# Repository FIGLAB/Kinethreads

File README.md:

# Kinethreads: Soft Full-Body Haptic Exosuit using Low-Cost Motor-Pulley Mechanisms
This is the repository for Kinethreads, presented at UIST 2025. Check out the [full paper here](https://drive.google.com/file/d/1RWJZLoprh9HyUMLJXVf4V8MswR2cnfrb/view?usp=sharing), as well as our [video](https://www.youtube.com/watch?v=4ev0w_tbuw8)!

Codebase will be updated soon!

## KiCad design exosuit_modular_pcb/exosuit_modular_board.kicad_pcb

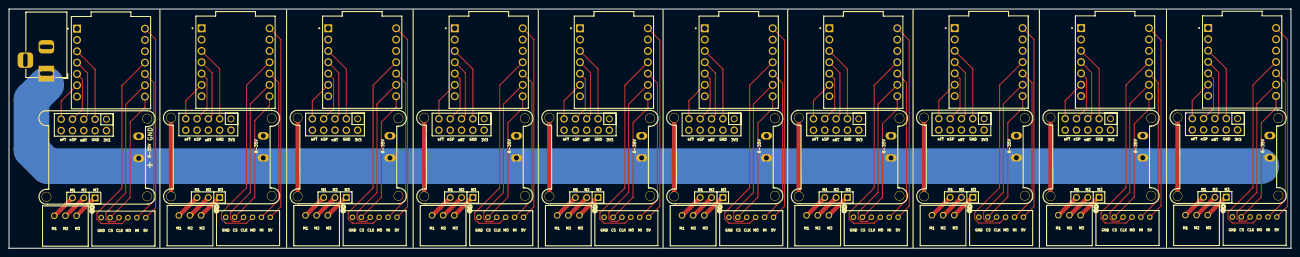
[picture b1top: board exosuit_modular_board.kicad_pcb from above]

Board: 2 copper layers, 287.6 x 53.7 mm, 56 parts (0 on the bottom side), 122 nets.

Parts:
BJ1: Barrel_Jack_Switch_Pin3Ring; BarrelJack_Horizontal
H1, H2, H3, H4, H5, H6, H7, H8, H9, H10: Female header2.54mm2*5p Straight; HDR-TH_10P-P2.54-V-F-R2-C5-S2.54
J1m1, J2m1, J3m1, J4m1, J5m1, J6m1, J7m1, J8m1, J9m1, J10m1: S3B-EH; CONN_S3B-EH_JST
J1s1, J2s1, J3s1, J4s1, J5s1, J6s1, J7s1, J8s1, J9s1, J10s1: S6B-PH-K-S; CONN_S6B-PH-K-S_JST
P1, P2, P3, P4, P5, P6, P7, P8, P9, P10: Header-Female-2.54_1x3; HDR-TH_3P-P2.54-V-F
Pad_gge5124: Pad_gge5124
Pad_gge5154: Pad_gge5154
Pad_gge5250: Pad_gge5250
Pad_gge5349: Pad_gge5349
Pad_gge7437: Pad_gge7437
U1, U2, U3, U4, U5, U6, U7, U8, U9, U10: ADAFRUIT_QT_PY; MODULE_ADAFRUIT_QT_PY

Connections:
GND: BJ1.2, BJ1.3, H1.1, H2.1, H3.1, H4.1, H5.1, H6.1, H7.1, H8.1, H9.1, H10.1, J1s1.1, J2s1.1, J3s1.1, J4s1.1, J5s1.1, J6s1.1, J7s1.1, J8s1.1, J9s1.1, J10s1.1, Pad_gge5124.2, Pad_gge5250.5, Pad_gge5349.5, Pad_gge7437.5, U1.13 (GND), U2.13 (GND), U3.13 (GND), U4.13 (GND), U5.13 (GND), U6.13 (GND), U7.13 (GND), U8.13 (GND), U9.13 (GND), U10.13 (GND)
unnamed: J1m1.1, P1.1
unnamed: J1m1.2, P1.2
unnamed: J1m1.3, P1.3
unnamed: J2m1.1, P2.1
unnamed: J2m1.2, P2.2
unnamed: J2m1.3, P2.3
unnamed: J3m1.1, P3.1
unnamed: J3m1.2, P3.2
unnamed: J3m1.3, P3.3
unnamed: J4m1.1, P4.1
unnamed: J4m1.2, P4.2
unnamed: J4m1.3, P4.3
unnamed: J5m1.1, P5.1
unnamed: J5m1.2, P5.2
unnamed: J5m1.3, P5.3
unnamed: J6m1.1, P6.1
unnamed: J6m1.2, P6.2
unnamed: J6m1.3, P6.3
unnamed: J7m1.1, P7.1
unnamed: J7m1.2, P7.2
unnamed: J7m1.3, P7.3
unnamed: J8m1.1, P8.1
unnamed: J8m1.2, P8.2
unnamed: J8m1.3, P8.3
unnamed: J9m1.1, P9.1
unnamed: J9m1.2, P9.2
unnamed: J9m1.3, P9.3
unnamed: J10m1.1, P10.1
unnamed: J10m1.2, P10.2
unnamed: J10m1.3, P10.3
unnamed: J1s1.6, U1.14 (5V)
unnamed: H1.3, U1.3 (A2/D2)
unnamed: H1.5, U1.4 (A3/D3)
unnamed: J1s1.2, U1.8 (A7/D7/RX)
unnamed: J1s1.3, U1.9 (A8/D8/SCK)
unnamed: J1s1.5, U1.10 (A9/D9/MISO)
unnamed: J1s1.4, U1.11 (A10/D10/MOSI)
unnamed: H1.7, U1.5 (D4/SDA)
unnamed: H1.9, U1.6 (D5/SCL)
unnamed: J2s1.6, U2.14 (5V)
unnamed: H2.3, U2.3 (A2/D2)
unnamed: H2.5, U2.4 (A3/D3)
unnamed: J2s1.2, U2.8 (A7/D7/RX)
unnamed: J2s1.3, U2.9 (A8/D8/SCK)
unnamed: J2s1.5, U2.10 (A9/D9/MISO)
unnamed: J2s1.4, U2.11 (A10/D10/MOSI)
unnamed: H2.7, U2.5 (D4/SDA)
unnamed: H2.9, U2.6 (D5/SCL)
unnamed: J3s1.6, U3.14 (5V)
unnamed: H3.3, U3.3 (A2/D2)
unnamed: H3.5, U3.4 (A3/D3)
unnamed: J3s1.2, U3.8 (A7/D7/RX)
unnamed: J3s1.3, U3.9 (A8/D8/SCK)
unnamed: J3s1.5, U3.10 (A9/D9/MISO)
unnamed: J3s1.4, U3.11 (A10/D10/MOSI)
unnamed: H3.7, U3.5 (D4/SDA)
unnamed: H3.9, U3.6 (D5/SCL)
unnamed: J4s1.6, U4.14 (5V)
unnamed: H4.3, U4.3 (A2/D2)
unnamed: H4.5, U4.4 (A3/D3)
unnamed: J4s1.2, U4.8 (A7/D7/RX)
unnamed: J4s1.3, U4.9 (A8/D8/SCK)
unnamed: J4s1.5, U4.10 (A9/D9/MISO)
unnamed: J4s1.4, U4.11 (A10/D10/MOSI)
unnamed: H4.7, U4.5 (D4/SDA)
unnamed: H4.9, U4.6 (D5/SCL)
unnamed: J5s1.6, U5.14 (5V)
unnamed: H5.3, U5.3 (A2/D2)
unnamed: H5.5, U5.4 (A3/D3)
unnamed: J5s1.2, U5.8 (A7/D7/RX)
unnamed: J5s1.3, U5.9 (A8/D8/SCK)
unnamed: J5s1.5, U5.10 (A9/D9/MISO)
unnamed: J5s1.4, U5.11 (A10/D10/MOSI)
unnamed: H5.7, U5.5 (D4/SDA)
unnamed: H5.9, U5.6 (D5/SCL)
unnamed: J6s1.6, U6.14 (5V)
unnamed: H6.3, U6.3 (A2/D2)
unnamed: H6.5, U6.4 (A3/D3)
unnamed: J6s1.2, U6.8 (A7/D7/RX)
unnamed: J6s1.3, U6.9 (A8/D8/SCK)
unnamed: J6s1.5, U6.10 (A9/D9/MISO)
unnamed: J6s1.4, U6.11 (A10/D10/MOSI)
unnamed: H6.7, U6.5 (D4/SDA)
unnamed: H6.9, U6.6 (D5/SCL)
unnamed: J7s1.6, U7.14 (5V)
unnamed: H7.3, U7.3 (A2/D2)
unnamed: H7.5, U7.4 (A3/D3)
unnamed: J7s1.2, U7.8 (A7/D7/RX)
unnamed: J7s1.3, U7.9 (A8/D8/SCK)
unnamed: J7s1.5, U7.10 (A9/D9/MISO)
unnamed: J7s1.4, U7.11 (A10/D10/MOSI)
unnamed: H7.7, U7.5 (D4/SDA)
unnamed: H7.9, U7.6 (D5/SCL)
unnamed: J8s1.6, U8.14 (5V)
unnamed: H8.3, U8.3 (A2/D2)
unnamed: H8.5, U8.4 (A3/D3)
unnamed: J8s1.2, U8.8 (A7/D7/RX)
unnamed: J8s1.3, U8.9 (A8/D8/SCK)
unnamed: J8s1.5, U8.10 (A9/D9/MISO)
unnamed: J8s1.4, U8.11 (A10/D10/MOSI)
unnamed: H8.7, U8.5 (D4/SDA)
unnamed: H8.9, U8.6 (D5/SCL)
unnamed: J9s1.6, U9.14 (5V)
unnamed: H9.3, U9.3 (A2/D2)
unnamed: H9.5, U9.4 (A3/D3)
unnamed: J9s1.2, U9.8 (A7/D7/RX)
unnamed: J9s1.3, U9.9 (A8/D8/SCK)
unnamed: J9s1.5, U9.10 (A9/D9/MISO)
unnamed: J9s1.4, U9.11 (A10/D10/MOSI)
unnamed: H9.7, U9.5 (D4/SDA)
unnamed: H9.9, U9.6 (D5/SCL)
unnamed: J10s1.6, U10.14 (5V)
unnamed: H10.3, U10.3 (A2/D2)
unnamed: H10.5, U10.4 (A3/D3)
unnamed: J10s1.2, U10.8 (A7/D7/RX)
unnamed: J10s1.3, U10.9 (A8/D8/SCK)
unnamed: J10s1.5, U10.10 (A9/D9/MISO)
unnamed: J10s1.4, U10.11 (A10/D10/MOSI)
unnamed: H10.7, U10.5 (D4/SDA)
unnamed: H10.9, U10.6 (D5/SCL)
VCC: BJ1.1, Pad_gge5154.3

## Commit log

2025-11-06 adding the pcb files
2025-11-06 adding unity project slowly
2025-11-06 still adding unity slowly
2025-11-06 more unity incoming
2025-11-06 last of unity?
2025-11-06 final gitignore edit
